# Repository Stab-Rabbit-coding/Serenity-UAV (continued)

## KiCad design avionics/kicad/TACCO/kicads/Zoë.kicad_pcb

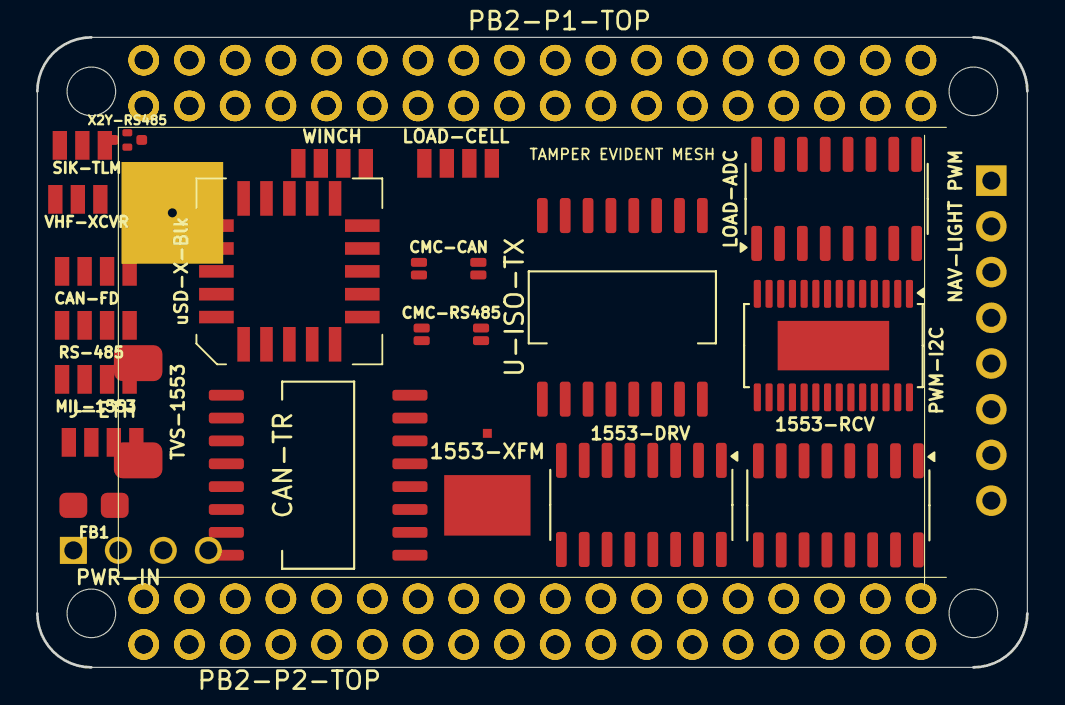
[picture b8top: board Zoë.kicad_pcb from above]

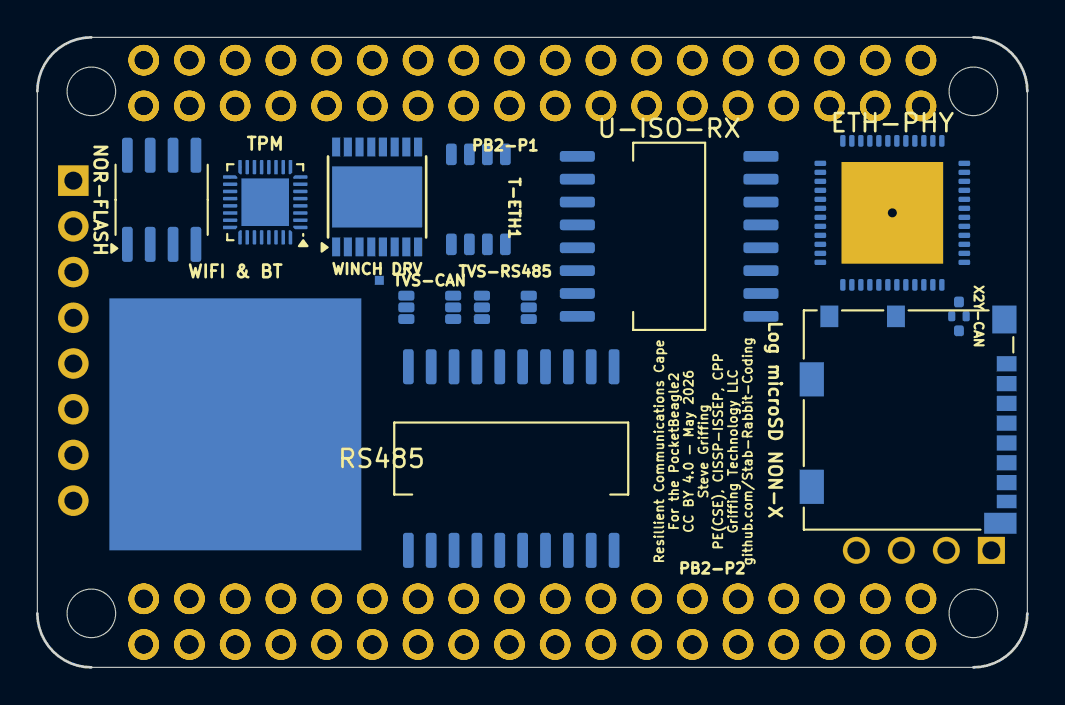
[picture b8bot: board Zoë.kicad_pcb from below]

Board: 4 copper layers, 55.0 x 35.0 mm, 39 parts (14 on the bottom side), 85 nets, no tracks yet.

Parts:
1553-DRV: DS26LV31; SOIC-16_3.9x9.9mm_P1.27mm
1553-RCV: DS26LV32; SOIC-16_3.9x9.9mm_P1.27mm
1553-XFM: SM-1553-11; Package
CAN-FD: JST-GH-4P-CAN; JST_GH_4P
CAN-TR: ISOW1044BDFMR; SOIC-16W_7.5x10.3mm_P1.27mm
CMC-CAN: SRF2012-100Y; Bourns_SRF2012_4T
CMC-RS485: SRF2012-100Y; Bourns_SRF2012_4T
ETH-PHY: ADIN1300BCPZ; QFN-48-1EP_7x7mm_P0.5mm_EP5.65x5.65mm
FB1: 742792512; C_0805_2012Metric
J-ETH: JST-GH-4P-ETH; JST_GH_4P
LOAD-ADC: HX711; SOIC-16_3.9x9.9mm_P1.27mm
LOAD-CELL: JST-GH-4P-LOAD-CELL; JST_GH_4P
Log microSD NON-X: microSD-Log; microSD_HC_Molex_104031-0811
MIL-1553: JST-GH-4P-1553; JST_GH_4P
NAV-LIGHT PWM: 1x8-NavLight-PWM; Connector_PinHeader_2.54mm
NOR-FLASH: W25Q128JV; SOIC-8_3.9x4.9mm_P1.27mm
PB2-P1, PB2-P1-TOP: PB2I-P1-2x18; 2x18_P1_Socket
PB2-P2, PB2-P2-TOP: PB2I-P2-2x18; 2x18_P2_Socket
PWM-I2C: PCA9685; HTSSOP-28-1EP_4.4x9.7mm_P0.65mm_EP2.75x6.2mm
PWR-IN: Nano-Fit-4P-POWER; Connector_Molex_NanoFit
RS485: ADM2795EBRWZ; SOIC-20W_7.5x12.8mm_P1.27mm
RS-485: JST-GH-4P-RS485; JST_GH_4P
SIK-TLM: JST-GH-3P-SiK; JST_GH_3P
T-ETH1: 749010012A; ETH_XFMR_8P_5x3.5mm
TPM: SLB9670; QFN-32-1EP_4x4mm_P0.4mm_EP2.65x2.65mm
TVS-1553: SMAJ33CA; DO-214AC_SMA
TVS-CAN: PRTR5V0U2X; SOT-363_SC-88
TVS-RS485: PRTR5V0U2X; SOT-363_SC-88
U-ISO-RX: ISO7642FDWRR; SOIC-16W_7.5x10.3mm_P1.27mm
U-ISO-TX: ISO7642FDWRR; SOIC-16W_7.5x10.3mm_P1.27mm
VHF-XCVR: JST-GH-3P-XCVR-49MHZ; JST_GH_3P
WIFI & BT: WL1837MOD; RF_Module
WINCH: JST-GH-4P-WINCH; JST_GH_4P
WINCH DRV: DRV8833; HTSSOP-16-1EP_4.4x5mm_P0.65mm_EP3.4x5mm
X2Y-CAN, X2Y-RS485: 4.7nF X2Y; X2Y_Cap_4T_0402
uSD-X-Blk: ATF16V8BQL; PLCC-20

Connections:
+3V3: CAN-TR.1, PB2-P1.33, PB2-P1.34, PB2-P1-TOP.33, PB2-P1-TOP.34, RS485.1, U-ISO-RX.16, U-ISO-TX.1
+5V: FB1.1, FB1.2, PB2-P1.35, PB2-P1-TOP.35, PB2-P2.35, PB2-P2-TOP.35
CAN_H: CAN-TR.9, CMC-CAN.1, CMC-CAN.3, TVS-CAN.1
CAN_L: CAN-TR.10, CMC-CAN.2, CMC-CAN.4, TVS-CAN.3
CAN_STB: CAN-TR.3, PB2-P1.12, PB2-P1-TOP.12
ETH_LINE_RXN: J-ETH.4, T-ETH1.8
ETH_LINE_RXP: J-ETH.3, T-ETH1.7
ETH_LINE_TXN: J-ETH.2, T-ETH1.6
ETH_LINE_TXP: J-ETH.1, T-ETH1.5
ETH_RXN: ETH-PHY.5, T-ETH1.4
ETH_RXP: ETH-PHY.4, T-ETH1.3
ETH_TXN: ETH-PHY.2, T-ETH1.2
ETH_TXP: ETH-PHY.1, T-ETH1.1
GND: CAN-TR.8, ETH-PHY.3, ETH-PHY.6, ETH-PHY.10, ETH-PHY.11, ETH-PHY.12, ETH-PHY.49, PB2-P1.1, PB2-P1.2, PB2-P1.36, PB2-P1-TOP.1, PB2-P1-TOP.2, PB2-P1-TOP.36, PB2-P2.36, PB2-P2-TOP.36, RS485.2, RS485.7, RS485.8, TVS-1553.1, U-ISO-RX.9, U-ISO-TX.8, X2Y-CAN.1, X2Y-CAN.2, X2Y-CAN.3, X2Y-RS485.1, X2Y-RS485.2, X2Y-RS485.3
GND2_CAN: CAN-TR.12, CAN-TR.13, TVS-CAN.2, X2Y-CAN.4
GND2_ETH: ETH-PHY.21, ETH-PHY.22, ETH-PHY.25, ETH-PHY.34, ETH-PHY.36, U-ISO-RX.8, U-ISO-TX.9
GND2_RS485: RS485.12, RS485.13, RS485.18, RS485.19, TVS-RS485.2, X2Y-RS485.4
I2C0_SCL: PB2-P1.4, PB2-P1-TOP.4, PWM-I2C.24
I2C0_SDA: PB2-P1.3, PB2-P1-TOP.3, PWM-I2C.22
LOAD_CELL_DOUT: PB2-P2.7, PB2-P2-TOP.7
LOAD_CELL_SCK: LOAD-ADC.16, PB2-P2.8, PB2-P2-TOP.8
LORA_DIO0: PB2-P1.20, PB2-P1-TOP.20
LORA_RESETN: PB2-P1.19, PB2-P1-TOP.19
MCAN1_RX: CAN-TR.4, PB2-P1.13, PB2-P1-TOP.13
MCAN1_TX: CAN-TR.2, PB2-P1.14, PB2-P1-TOP.14
MDC: ETH-PHY.19, PB2-P2.18, PB2-P2-TOP.18, U-ISO-TX.6, U-ISO-TX.11
MDIO: ETH-PHY.18, PB2-P2.17, PB2-P2-TOP.17, U-ISO-RX.7, U-ISO-RX.10
PHY1_INTRN: ETH-PHY.20, PB2-P2.16, PB2-P2-TOP.16, U-ISO-RX.6, U-ISO-RX.11
PHY1_RSTN: ETH-PHY.35, PB2-P2.15, PB2-P2-TOP.15, U-ISO-TX.7, U-ISO-TX.10
PHY2_INTRN: PB2-P2.14, PB2-P2-TOP.14
PHY2_RSTN: PB2-P2.13, PB2-P2-TOP.13
PRU_1553_RX_N: 1553-RCV.13, PB2-P1.5, PB2-P1-TOP.5
PRU_1553_RX_P: PB2-P1.6, PB2-P1-TOP.6
PRU_1553_TX_N: 1553-DRV.6, PB2-P1.7, PB2-P1-TOP.7
PRU_1553_TX_P: 1553-DRV.10, PB2-P1.8, PB2-P1-TOP.8
PWM_CH0: PB2-P2.6, PB2-P2-TOP.6, uSD-X-Blk.6
PWM_CH1: PB2-P2.5, PB2-P2-TOP.5, PWM-I2C.11, uSD-X-Blk.5
PWM_CH2: PB2-P2.4, PB2-P2-TOP.4, PWM-I2C.10, uSD-X-Blk.4
PWM_CH3: PB2-P2.3, PB2-P2-TOP.3, PWM-I2C.9, uSD-X-Blk.3
RMII0_CRS_DV: ETH-PHY.32, PB2-P2.29, PB2-P2-TOP.29, U-ISO-RX.4, U-ISO-RX.13
RMII0_REF_CLK: ETH-PHY.29, PB2-P2.27, PB2-P2-TOP.27, U-ISO-TX.2, U-ISO-TX.15
RMII0_RXD0: ETH-PHY.30, PB2-P2.31, PB2-P2-TOP.31, U-ISO-RX.2, U-ISO-RX.15
RMII0_RXD1: ETH-PHY.31, PB2-P2.30, PB2-P2-TOP.30, U-ISO-RX.3, U-ISO-RX.14
RMII0_RX_ER: ETH-PHY.33, PB2-P2.28, PB2-P2-TOP.28, U-ISO-RX.5, U-ISO-RX.12
RMII0_TXD0: ETH-PHY.28, PB2-P2.34, PB2-P2-TOP.34, U-ISO-TX.3, U-ISO-TX.14
RMII0_TXD1: ETH-PHY.27, PB2-P2.33, PB2-P2-TOP.33, U-ISO-TX.4, U-ISO-TX.13
RMII0_TX_EN: ETH-PHY.26, PB2-P2.32, PB2-P2-TOP.32, U-ISO-TX.5, U-ISO-TX.12
RMII1_CRS_DV: PB2-P2.21, PB2-P2-TOP.21
RMII1_REF_CLK: PB2-P2.19, PB2-P2-TOP.19
RMII1_RXD0: PB2-P2.23, PB2-P2-TOP.23
RMII1_RXD1: PB2-P2.22, PB2-P2-TOP.22
RMII1_RX_ER: PB2-P2.20, PB2-P2-TOP.20
RMII1_TXD0: PB2-P2.26, PB2-P2-TOP.26
RMII1_TXD1: PB2-P2.25, PB2-P2-TOP.25
RMII1_TX_EN: PB2-P2.24, PB2-P2-TOP.24
RS485_A: CMC-RS485.1, CMC-RS485.3, RS485.14, TVS-RS485.1
RS485_B: CMC-RS485.2, CMC-RS485.4, RS485.15, TVS-RS485.3
RS485_DE: PB2-P1.9, PB2-P1-TOP.9, RS485.4, RS485.5
RS485_RX: PB2-P1.10, PB2-P1-TOP.10, RS485.6
RS485_TX: PB2-P1.11, PB2-P1-TOP.11, RS485.3
SDIO_CLK: Log microSD NON-X.6, PB2-P1.32, PB2-P1-TOP.32
SDIO_CMD: Log microSD NON-X.8, PB2-P1.31, PB2-P1-TOP.31
SDIO_D0: Log microSD NON-X.4, PB2-P1.30, PB2-P1-TOP.30
SDIO_D1: PB2-P1.29, PB2-P1-TOP.29
SDIO_D2: Log microSD NON-X.3, PB2-P1.28, PB2-P1-TOP.28
SDIO_D3: PB2-P1.27, PB2-P1-TOP.27
SERVO6: PB2-P2.2, PB2-P2-TOP.2
SERVO7: PB2-P2.1, PB2-P2-TOP.1, uSD-X-Blk.15
SPI1_CLK: NOR-FLASH.2, PB2-P1.25, PB2-P1-TOP.25, TPM.23
SPI1_CS_LORA: PB2-P1.26, PB2-P1-TOP.26
SPI1_CS_NOR: NOR-FLASH.3, PB2-P1.22, PB2-P1-TOP.22
SPI1_CS_TPM: PB2-P1.21, PB2-P1-TOP.21, TPM.28
SPI1_MISO: NOR-FLASH.6, PB2-P1.23, PB2-P1-TOP.23, TPM.22
SPI1_MOSI: NOR-FLASH.5, PB2-P1.24, PB2-P1-TOP.24, TPM.21
TPM_IRQN: PB2-P2.12, PB2-P2-TOP.12, TPM.24
TPM_RSTN: PB2-P2.11, PB2-P2-TOP.11, TPM.1
UART_49MHZ_XCVR_RX: PB2-P1.15, PB2-P1-TOP.15
UART_49MHZ_XCVR_TX: PB2-P1.16, PB2-P1-TOP.16
UART_SIK_RX: PB2-P1.17, PB2-P1-TOP.17
UART_SIK_TX: PB2-P1.18, PB2-P1-TOP.18
VCC2_CAN: CAN-TR.14, TVS-CAN.5
VCC2_ETH: ETH-PHY.7, ETH-PHY.8, ETH-PHY.9, ETH-PHY.40, ETH-PHY.41, U-ISO-RX.1, U-ISO-TX.16
VCC2_RS485: RS485.11, RS485.20, TVS-RS485.5
WINCH_IN1: PB2-P2.10, PB2-P2-TOP.10, WINCH DRV.5
WINCH_IN2: PB2-P2.9, PB2-P2-TOP.9, WINCH DRV.8

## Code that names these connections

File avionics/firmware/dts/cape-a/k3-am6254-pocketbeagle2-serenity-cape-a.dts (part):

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#include <dt-bindings/net/ti-dp83867.h>

/* ───────────────────────────────────────────────────────────────────────────
 * GPIO line assignments on main_gpio0 — VERIFY AGAINST PB2 SCHEMATIC
 * Line numbers correspond to AM6254 GPIO bank 0 pins exposed on P1/P2.
 * ─────────────────────────────────────────────────────────────────────────*/
#define CAPE_A_GPIO_IMU_INT1        14  /* ICM-42688-P interrupt 1      [ESTIMATE] */
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    cape_a_spi0_pins: cape-a-spi0-pins {
        pinctrl-single,pins = <
            /* [CONFIRMED — k3-am625-sk.dtsi] */
            AM62X_IOPAD(0x01bc, PIN_INPUT,  0) /* (A13) SPI0_CLK              */
            AM62X_IOPAD(0x01c0, PIN_OUTPUT, 0) /* (B13) SPI0_D0   (MOSI)      */
            AM62X_IOPAD(0x01c4, PIN_INPUT,  0) /* (B12) SPI0_D1   (MISO)      */
        >;
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    cape_a_mcan0_pins: cape-a-mcan0-pins {
        pinctrl-single,pins = <
            /* [CONFIRMED — k3-am625-sk.dtsi] */
            AM62X_IOPAD(0x01d8, PIN_OUTPUT, 0) /* (C15) MCAN0_TX              */
            AM62X_IOPAD(0x01dc, PIN_INPUT,  0) /* (E15) MCAN0_RX              */
        >;
    };

    /* CPSW3G MDIO: shared MDC/MDIO bus for both DP83825I PHYs.          */
    cape_a_mdio_pins: cape-a-mdio-pins {
        pinctrl-single,pins = <
            /* [ESTIMATE — dedicated MDIO pad area] */
            AM62X_IOPAD(0x0160, PIN_OUTPUT,       0) /* MDC                    */
            AM62X_IOPAD(0x0164, PIN_INPUT_PULLUP, 0) /* MDIO                   */
        >;
    };

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    cape_a_rmii1_pins: cape-a-rmii1-pins {
        pinctrl-single,pins = <
            /* [ESTIMATE — RGMII1 pad area in RMII mux] */
            AM62X_IOPAD(0x0120, PIN_INPUT,  4) /* RMII1_RXD0                  */
            AM62X_IOPAD(0x0124, PIN_INPUT,  4) /* RMII1_RXD1                  */
            AM62X_IOPAD(0x0128, PIN_INPUT,  4) /* RMII1_RX_ER                 */
            AM62X_IOPAD(0x012c, PIN_INPUT,  4) /* RMII1_CRS_DV                */
            AM62X_IOPAD(0x0130, PIN_OUTPUT, 4) /* RMII1_TXD0                  */
            AM62X_IOPAD(0x0134, PIN_OUTPUT, 4) /* RMII1_TXD1                  */
            AM62X_IOPAD(0x0138, PIN_OUTPUT, 4) /* RMII1_TX_EN                 */
            AM62X_IOPAD(0x013c, PIN_INPUT,  4) /* RMII1_REF_CLK (50 MHz in)   */
        >;
    };

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    cape_a_rmii2_pins: cape-a-rmii2-pins {
        pinctrl-single,pins = <
            /* [ESTIMATE — RGMII2 pad area in RMII mux] */
            AM62X_IOPAD(0x0148, PIN_INPUT,  4) /* RMII2_RXD0                  */
            AM62X_IOPAD(0x014c, PIN_INPUT,  4) /* RMII2_RXD1                  */
            AM62X_IOPAD(0x0150, PIN_INPUT,  4) /* RMII2_RX_ER                 */
            AM62X_IOPAD(0x0154, PIN_INPUT,  4) /* RMII2_CRS_DV                */
            AM62X_IOPAD(0x0158, PIN_OUTPUT, 4) /* RMII2_TXD0                  */
            AM62X_IOPAD(0x015c, PIN_OUTPUT, 4) /* RMII2_TXD1                  */
            AM62X_IOPAD(0x0168, PIN_OUTPUT, 4) /* RMII2_TX_EN                 */
            AM62X_IOPAD(0x016c, PIN_INPUT,  4) /* RMII2_REF_CLK               */
        >;
    };

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    cape_a_pru1_pwm_pins: cape-a-pru1-pwm-pins {
        pinctrl-single,pins = <
            /* [ESTIMATE] */
            AM62X_IOPAD(0x00e0, PIN_OUTPUT, 5) /* PRG0_PRU1_GPO0 → SERVO6     */
            AM62X_IOPAD(0x00e4, PIN_OUTPUT, 5) /* PRG0_PRU1_GPO1 → SERVO7     */
        >;
    };
};
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
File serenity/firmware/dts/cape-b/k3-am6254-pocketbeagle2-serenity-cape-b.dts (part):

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 *               microSD (SPI mode, logging-only non-executable card)
 *   UART2     — RFD900x SiK 915 MHz (hardware CTS/RTS flow control)
 *   UART4     — MAX3485E RS-485 half-duplex (DE / RE# GPIOs)
 *   UART5     — XCVR-49MHZ-1 RCRS 49 MHz AX.25 (PTT_N + TDDS_SYNC GPIOs)
 *   MCAN0     — CAN FD 1/8 Mbps via ATA6561 transceiver (STB# GPIO)
 *   CPSW3G    — 100BASE-TX ring via 2× DP83825I RMII PHY
 *   SDIO      — WL1837MOD 5 GHz 802.11ac/b/g/n + BT5 (4-bit MMC)
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#include <dt-bindings/pinctrl/k3.h>

/* ───────────────────────────────────────────────────────────────────────────
 * GPIO line assignments on main_gpio0 — VERIFY AGAINST PB2 SCHEMATIC
 * All offsets relative to AM6254 GPIO bank 0 as exposed on P1/P2 headers.
 * ─────────────────────────────────────────────────────────────────────────*/

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#define CAPE_B_GPIO_LORA_RESET      20  /* RFM95W RESET (active-low)         [ESTIMATE] */

/* XCVR-49MHZ-1 RCRS 49 MHz control lines. */
#define CAPE_B_GPIO_PTT_N           21  /* PTT_N — TX key (active-low)       [ESTIMATE] */
#define CAPE_B_GPIO_TDDS_SYNC       22  /* Si5351A DDS freq sync strobe      [ESTIMATE] */

/* MAX3485E RS-485 direction control. */
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    cape_b_spi1_pins: cape-b-spi1-pins {
        pinctrl-single,pins = <
            /* [ESTIMATE — SPI1 pad area, verify in SPRUJ40 Table 7-1] */
            AM62X_IOPAD(0x01e0, PIN_INPUT,  0) /* SPI1_CLK                   */
            AM62X_IOPAD(0x01e4, PIN_OUTPUT, 0) /* SPI1_D0  (MOSI)            */
            AM62X_IOPAD(0x01e8, PIN_INPUT,  0) /* SPI1_D1  (MISO)            */
        >;
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    };

    /* UART5: XCVR-49MHZ-1 RCRS 49 MHz AX.25 link.
     * 57600 baud 8N1; PTT_N and TDDS_SYNC are GPIO (not UART signals).    */
    cape_b_uart5_pins: cape-b-uart5-pins {
        pinctrl-single,pins = <
            /* [ESTIMATE — GPMC0_AD area, mux4] */
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    cape_b_mcan0_pins: cape-b-mcan0-pins {
        pinctrl-single,pins = <
            /* [CONFIRMED — k3-am625-sk.dtsi] */
            AM62X_IOPAD(0x01d8, PIN_OUTPUT, 0) /* (C15) MCAN0_TX             */
            AM62X_IOPAD(0x01dc, PIN_INPUT,  0) /* (E15) MCAN0_RX             */
        >;
    };

    /* CPSW3G MDIO: shared MDC/MDIO bus for both DP83825I PHYs.           */
    cape_b_mdio_pins: cape-b-mdio-pins {
        pinctrl-single,pins = <
            /* [ESTIMATE — dedicated MDIO pad area] */
            AM62X_IOPAD(0x0160, PIN_OUTPUT,       0) /* MDC                   */
            AM62X_IOPAD(0x0164, PIN_INPUT_PULLUP, 0) /* MDIO                  */
        >;
    };

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    cape_b_rmii1_pins: cape-b-rmii1-pins {
        pinctrl-single,pins = <
            /* [ESTIMATE — RGMII1 pad area, mux4 for RMII] */
            AM62X_IOPAD(0x0120, PIN_INPUT,  4) /* RMII1_RXD0                 */
            AM62X_IOPAD(0x0124, PIN_INPUT,  4) /* RMII1_RXD1                 */
            AM62X_IOPAD(0x0128, PIN_INPUT,  4) /* RMII1_RX_ER                */
            AM62X_IOPAD(0x012c, PIN_INPUT,  4) /* RMII1_CRS_DV               */
            AM62X_IOPAD(0x0130, PIN_OUTPUT, 4) /* RMII1_TXD0                 */
            AM62X_IOPAD(0x0134, PIN_OUTPUT, 4) /* RMII1_TXD1                 */
            AM62X_IOPAD(0x0138, PIN_OUTPUT, 4) /* RMII1_TX_EN                */
            AM62X_IOPAD(0x013c, PIN_INPUT,  4) /* RMII1_REF_CLK (50 MHz in)  */
        >;
    };

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    cape_b_rmii2_pins: cape-b-rmii2-pins {
        pinctrl-single,pins = <
            /* [ESTIMATE — RGMII2 pad area, mux4 for RMII] */
            AM62X_IOPAD(0x0148, PIN_INPUT,  4) /* RMII2_RXD0                 */
            AM62X_IOPAD(0x014c, PIN_INPUT,  4) /* RMII2_RXD1                 */
            AM62X_IOPAD(0x0150, PIN_INPUT,  4) /* RMII2_RX_ER                */
            AM62X_IOPAD(0x0154, PIN_INPUT,  4) /* RMII2_CRS_DV               */
            AM62X_IOPAD(0x0158, PIN_OUTPUT, 4) /* RMII2_TXD0                 */
            AM62X_IOPAD(0x015c, PIN_OUTPUT, 4) /* RMII2_TXD1                 */
            AM62X_IOPAD(0x0168, PIN_OUTPUT, 4) /* RMII2_TX_EN                */
            AM62X_IOPAD(0x016c, PIN_INPUT,  4) /* RMII2_REF_CLK              */
        >;
    };

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};

/* UART5: XCVR-49MHZ-1 RCRS 49 MHz AX.25 link.
 * 57600 baud 8N1.  PTT_N (CAPE_B_GPIO_PTT_N) and TDDS_SYNC
 * (CAPE_B_GPIO_TDDS_SYNC) are managed by the serenity-cn daemon via
 * libgpiod 2.x; they are not modelled as UART modem control lines.
 *
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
